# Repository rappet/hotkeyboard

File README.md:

# Stimboard

A small two key USB keyboard inspired by a stimming tool

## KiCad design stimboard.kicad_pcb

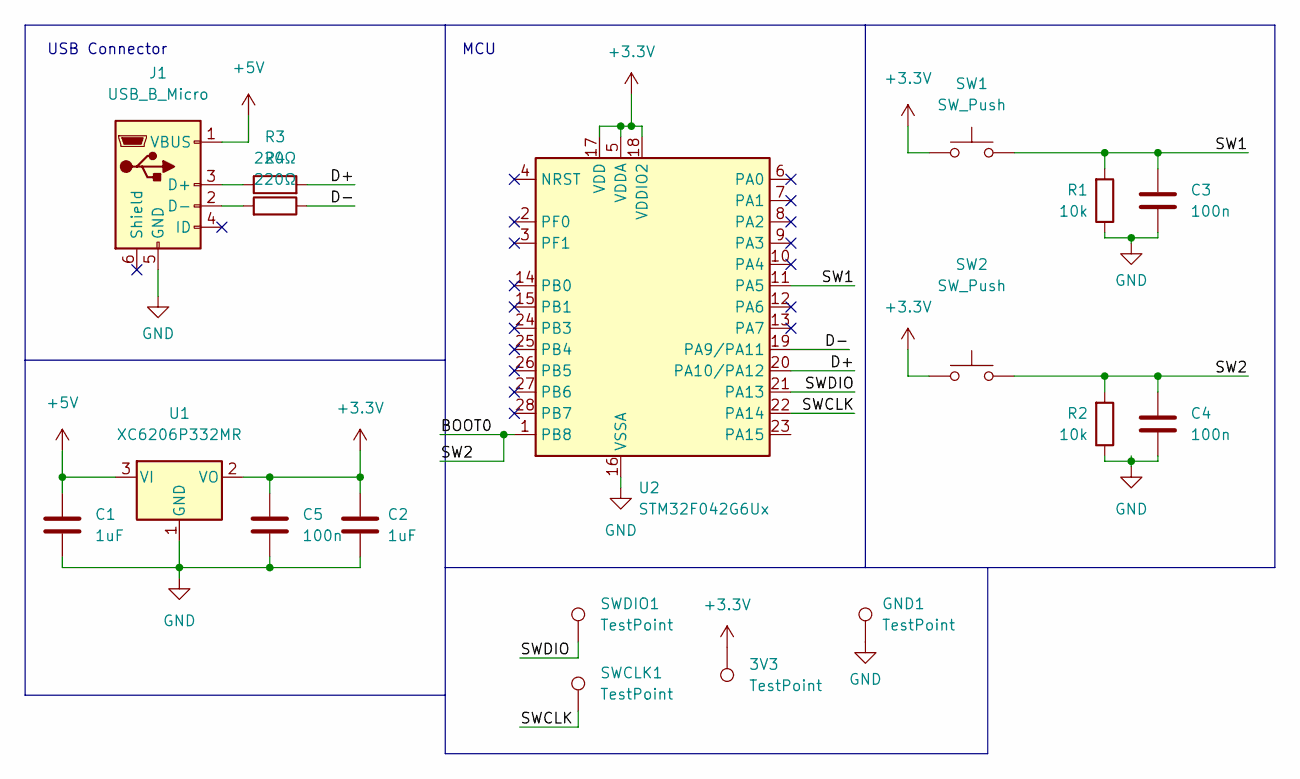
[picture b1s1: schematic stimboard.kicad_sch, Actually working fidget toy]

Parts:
3V3: TestPoint; TestPoint_Pad_1.0x1.0mm
C1, C2: 1uF; C_0402_1005Metric; LCSC C15849
C3, C4, C5: 100n; C_0402_1005Metric
GND1: TestPoint; TestPoint_Pad_1.0x1.0mm
J1: USB_B_Micro; USB_Micro-B_Amphenol_10103594-0001LF_Horizontal; LCSC C428495
R1, R2: 10k; R_0402_1005Metric; LCSC C25086
R3, R4: 220Ω; R_0402_1005Metric
SW1, SW2: SW_Push; SW_Cherry_MX_1.00u_PCB
SWCLK1: TestPoint; TestPoint_Pad_1.0x1.0mm
SWDIO1: TestPoint; TestPoint_Pad_1.0x1.0mm
U1: XC6206P332MR; SOT-23; LCSC C5446
U2: STM32F042G6Ux; QFN-28_4x4mm_P0.5mm

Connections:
+3.3V: 3V3.1, C2.1, C5.1, SW1.2, SW2.1, U1.2 (VO), U2.5 (VDDA), U2.17 (VDD), U2.18 (VDDIO2)
+5V: C1.1, J1.1 (VBUS), U1.3 (VI)
/BOOT0: C4.1, R2.2, SW2.2, U2.1 (PB8)
/D+: R3.2, U2.20 (PA10/PA12)
/D-: R4.1, U2.19 (PA9/PA11)
/SW1: C3.1, R1.2, SW1.1, U2.11 (PA5)
/SWCLK: SWCLK1.1, U2.22 (PA14)
/SWDIO: SWDIO1.1, U2.21 (PA13)
GND: C1.2, C2.2, C3.2, C4.2, C5.2, GND1.1, J1.5 (GND), R1.1, R2.1, U1.1 (GND), U2.16 (VSSA)
unnamed: J1.2 (D-), R4.2
unnamed: J1.3 (D+), R3.1

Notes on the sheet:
USB Connector
MCU

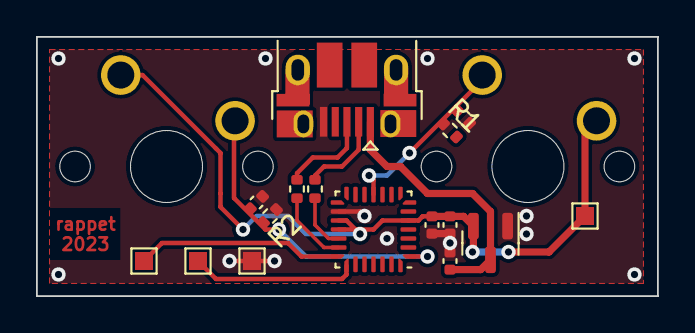
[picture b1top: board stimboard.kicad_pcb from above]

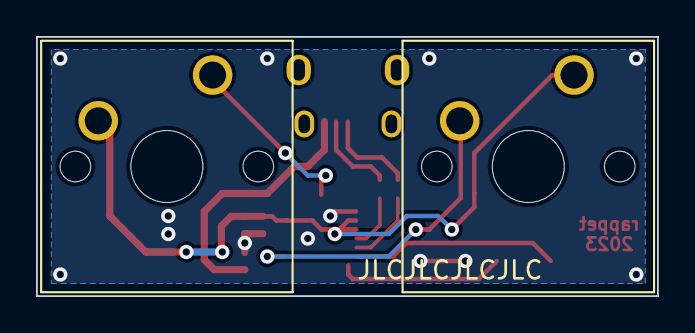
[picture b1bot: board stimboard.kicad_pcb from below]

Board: 2 copper layers, 34.5 x 14.4 mm, 18 parts (2 on the bottom side), 11 nets.

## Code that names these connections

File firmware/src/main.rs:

#![no_std]
#![no_main]

extern crate panic_halt;

use cortex_m_rt::entry;
use defmt::info;
#[cfg(feature = "defmt")]
use defmt_rtt as _;
use stm32f0xx_hal::{
    pac,
    prelude::*,
    rcc::USBClockSource,
    time::Hertz,
    timers::Timer,
    usb::{Peripheral, UsbBus as StmUsbBus},
};
use usb_device::prelude::*;
use usbd_human_interface_device::{
    device::{
        consumer::{ConsumerControlConfig, MultipleConsumerReport},
        keyboard::BootKeyboardConfig,
    },
    page::{Consumer, Keyboard},
    usb_class::UsbHidClassBuilder,
};

mod parameters;

#[derive(Copy, Clone)]
// Allow dead code as certain action might or might not be used depending on config
#[allow(dead_code)]
pub(crate) enum Action {
    Keyboard(Keyboard),
    Consumer(Consumer),
}

#[entry]
fn main() -> ! {
    let mut dp = pac::Peripherals::take().unwrap();

    // Remap so USB works
    stm32f0xx_hal::usb::remap_pins(&mut dp.RCC, &mut dp.SYSCFG);

    let mut rcc = dp
        .RCC
        .configure()
        .hsi48()
        .enable_crs(dp.CRS)
        .sysclk(48.mhz())
        .pclk(24.mhz())
        .usbsrc(USBClockSource::HSI48)
        .freeze(&mut dp.FLASH);

    // Configure the on-board LED (LD3, green)
    let gpioa = dp.GPIOA.split(&mut rcc);
    let gpiob = dp.GPIOB.split(&mut rcc);
    //let mut led = cortex_m::interrupt::free(|cs| gpiob.pb3.into_push_pull_output(cs));
    let left_key = cortex_m::interrupt::free(|cs| gpioa.pa5.into_floating_input(cs));
    let right_key = cortex_m::interrupt::free(|cs| gpiob.pb8.into_pull_down_input(cs));

    let mut timer = Timer::tim1(dp.TIM1, Hertz(1000), &mut rcc);

    let usb = Peripheral {
        usb: dp.USB,
        pin_dm: gpioa.pa11,
        pin_dp: gpioa.pa12,
    };

    let usb_allocator = StmUsbBus::new(usb);

    let mut keyboard = UsbHidClassBuilder::new()
        .add_device(BootKeyboardConfig::default())
        .build(&usb_allocator);
    let mut consumer_device = UsbHidClassBuilder::new()
        .add_device(ConsumerControlConfig::default())
        .build(&usb_allocator);

    let mut usb_dev = UsbDeviceBuilder::new(
        &usb_allocator,
        UsbVidPid(parameters::USB_VID, parameters::USB_PID),
    )
    .manufacturer(parameters::USB_MANUFACTURER)
    .product(parameters::USB_PRODUCT)
    .serial_number(parameters::USB_SERIAL_NUMBER)
    .build();

    timer.start(Hertz(1000));

    let mut i = 0u32;

    info!("start main loop");

    loop {
        i = i.wrapping_add(1);

        if i % 10 == 0 {
            let left = left_key.is_high().unwrap();
            let right = right_key.is_high().unwrap();

            let keys = [
                match parameters::LEFT_KEY {
                    Action::Keyboard(key) if left => key,
                    _ => Keyboard::NoEventIndicated,
                },
                match parameters::RIGHT_KEY {
                    Action::Keyboard(key) if right => key,
                    _ => Keyboard::NoEventIndicated,
                },
            ];

            keyboard.device().write_report(keys).ok();

            let consumers = [
                match parameters::LEFT_KEY {
                    Action::Consumer(consumer) if left => consumer,
                    _ => Consumer::Unassigned,
                },
                match parameters::RIGHT_KEY {
                    Action::Consumer(consumer) if right => consumer,
                    _ => Consumer::Unassigned,
                },
                Consumer::Unassigned,
                Consumer::Unassigned,
            ];

            consumer_device
                .device()
                .write_report(&MultipleConsumerReport { codes: consumers })
                .ok();
        }

        keyboard.tick().ok();
        consumer_device.tick().ok();

        if nb::block!(timer.wait()).is_ok() {
            keyboard.tick().unwrap();
        }

        if usb_dev.poll(&mut [&mut keyboard, &mut consumer_device]) {
            let _ = keyboard.device().read_report();
        }
    }
}

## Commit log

2023-06-27 Funky version
2023-07-29 Add firmware
2023-07-29 firmware: Remove wrong commend copied from template
2023-07-29 firmware: Add consumer device
